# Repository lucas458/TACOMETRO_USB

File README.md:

# TACOMETRO USB
## Tacômetro USB para jogos usando PIC12F1822.

#### Placa

### Os dados a serem enviados são compostos por 6 bytes e serão transmitidos pela porta serial.
| Buffer Index | Valor (decimal) | Descrição |
| ------------ | --------------- | --------- |
| 0 | 0 a 255 | Digito 0 |
| 1 | 0 a 255 | Digito 1 |
| 2 | 0 a 255 | Digito 2 |
| 3 | 0 a 20 | Quantidade de LEDS ligados |
| 4 | 0 a 15 | Brilho |
| 5 | '\r' ou '\n' | **Caractere obrigatório** |

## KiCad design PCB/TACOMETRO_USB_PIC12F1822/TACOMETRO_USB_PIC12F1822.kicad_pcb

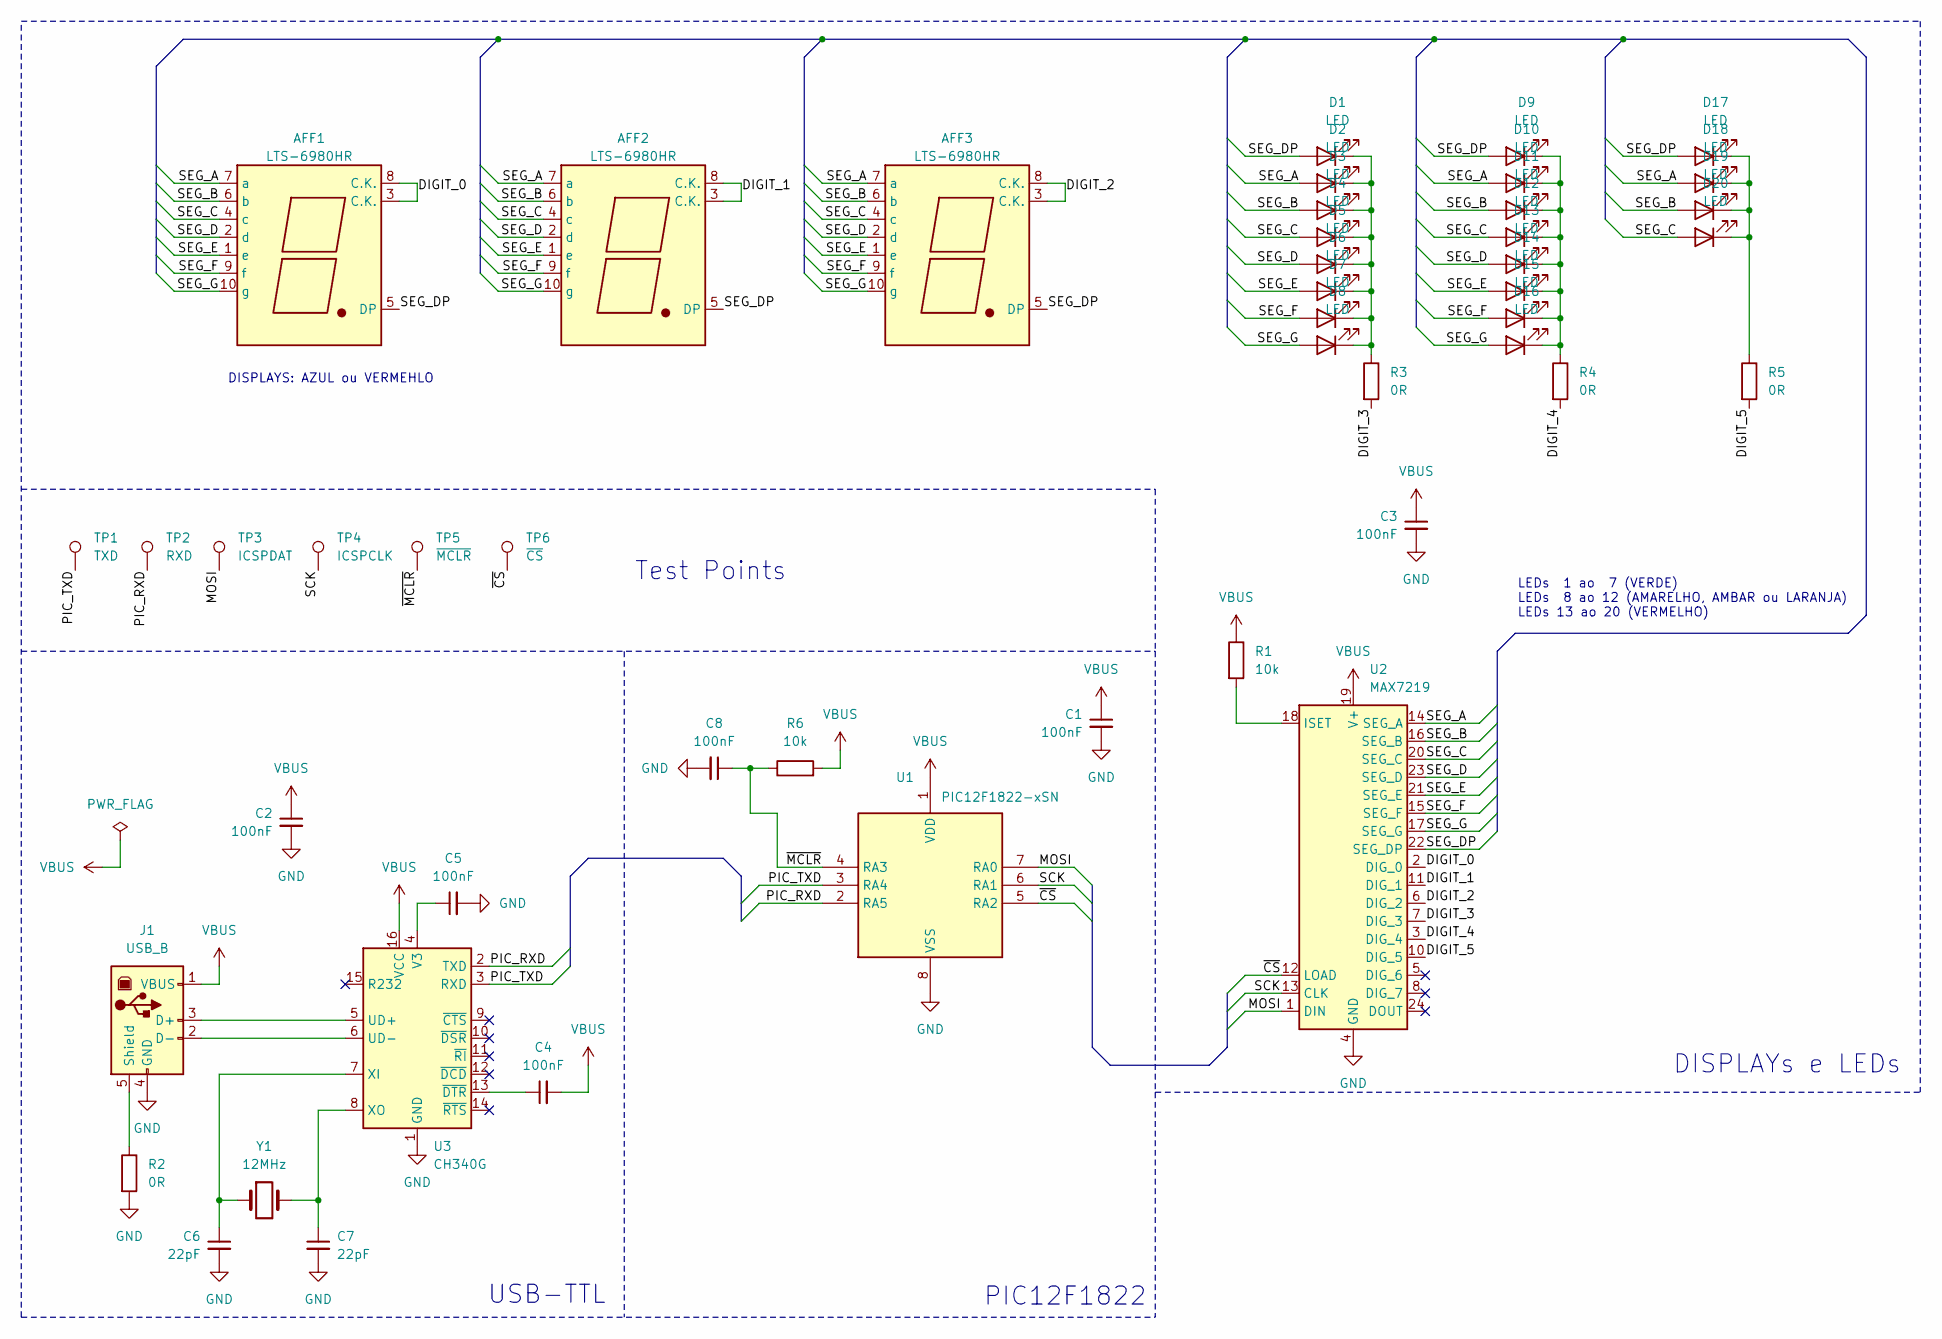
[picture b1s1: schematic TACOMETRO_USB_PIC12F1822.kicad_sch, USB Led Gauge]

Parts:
AFF1, AFF2, AFF3: LTS-6980HR; 7SegmentLED_LTS6760_LTS6780
C1, C2, C3, C4, C5, C8: 100nF; C_0603_1608Metric
C6, C7: 22pF; C_0603_1608Metric
D1, D2, D3, D4, D5, D6, D7, D8, D9, D10, D11, D12, D13, D14, D15, D16, D17, D18, D19, D20: LED; LED_D5.0mm_Clear
J1: USB_B; 5787834-1
R1, R6: 10k; R_0603_1608Metric
R2, R3, R4, R5: 0R; R_0603_1608Metric
TP1: TXD; TestPoint_Pad_D1.0mm
TP2: RXD; TestPoint_Pad_D1.0mm
TP3: ICSPDAT; TestPoint_Pad_D1.0mm
TP4: ICSPCLK; TestPoint_Pad_D1.0mm
TP5: ~{MCLR}; TestPoint_Pad_D1.0mm
TP6: ~{CS}; TestPoint_Pad_D1.0mm
U1: PIC12F1822-xSN; SOIC-8_3.9x4.9mm_P1.27mm
U2: MAX7219; SOIC-24W_7.5x15.4mm_P1.27mm
U3: CH340G; SOIC-16_3.9x9.9mm_P1.27mm
Y1: 12MHz; Crystal_HC49-U_Vertical

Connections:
/DIGIT_0: AFF1.3 (C.K.), AFF1.8 (C.K.), U2.2 (DIG_0)
/DIGIT_1: AFF2.3 (C.K.), AFF2.8 (C.K.), U2.11 (DIG_1)
/DIGIT_2: AFF3.3 (C.K.), AFF3.8 (C.K.), U2.6 (DIG_2)
/DIGIT_3: R3.2, U2.7 (DIG_3)
/DIGIT_4: R4.2, U2.3 (DIG_4)
/DIGIT_5: R5.2, U2.10 (DIG_5)
/MOSI: TP3.1, U1.7 (RA0), U2.1 (DIN)
/PIC_RXD: TP2.1, U1.2 (RA5), U3.2 (TXD)
/PIC_TXD: TP1.1, U1.3 (RA4), U3.3 (RXD)
/SCK: TP4.1, U1.6 (RA1), U2.13 (CLK)
/SEG_A: AFF1.7 (a), AFF2.7 (a), AFF3.7 (a), D2.2 (A), D10.2 (A), D18.2 (A), U2.14 (SEG_A)
/SEG_B: AFF1.6 (b), AFF2.6 (b), AFF3.6 (b), D3.2 (A), D11.2 (A), D19.2 (A), U2.16 (SEG_B)
/SEG_C: AFF1.4 (c), AFF2.4 (c), AFF3.4 (c), D4.2 (A), D12.2 (A), D20.2 (A), U2.20 (SEG_C)
/SEG_D: AFF1.2 (d), AFF2.2 (d), AFF3.2 (d), D5.2 (A), D13.2 (A), U2.23 (SEG_D)
/SEG_DP: AFF1.5 (DP), AFF2.5 (DP), AFF3.5 (DP), D1.2 (A), D9.2 (A), D17.2 (A), U2.22 (SEG_DP)
/SEG_E: AFF1.1 (e), AFF2.1 (e), AFF3.1 (e), D6.2 (A), D14.2 (A), U2.21 (SEG_E)
/SEG_F: AFF1.9 (f), AFF2.9 (f), AFF3.9 (f), D7.2 (A), D15.2 (A), U2.15 (SEG_F)
/SEG_G: AFF1.10 (g), AFF2.10 (g), AFF3.10 (g), D8.2 (A), D16.2 (A), U2.17 (SEG_G)
/~CS: TP6.1, U1.5 (RA2), U2.12 (LOAD)
/~MCLR: C8.1, R6.1, TP5.1, U1.4 (RA3)
GND: C1.2, C2.2, C3.2, C5.2, C6.2, C7.2, C8.2, J1.4 (GND), R2.2, U1.8 (VSS), U2.4 (GND), U2.9 (GND), U3.1 (GND)
unnamed: D1.1 (K), D2.1 (K), D3.1 (K), D4.1 (K), D5.1 (K), D6.1 (K), D7.1 (K), D8.1 (K), R3.1
unnamed: D9.1 (K), D10.1 (K), D11.1 (K), D12.1 (K), D13.1 (K), D14.1 (K), D15.1 (K), D16.1 (K), R4.1
unnamed: D17.1 (K), D18.1 (K), D19.1 (K), D20.1 (K), R5.1
unnamed: J1.3 (D+), U3.5 (UD+)
unnamed: J1.2 (D-), U3.6 (UD-)
unnamed: J1.5 (Shield), R2.1
unnamed: R1.2, U2.18 (ISET)
unnamed: C5.1, U3.4 (V3)
unnamed: C6.1, U3.7 (XI), Y1.1
unnamed: C7.1, U3.8 (XO), Y1.2
unnamed: C4.1, U3.13 (~DTR)
VBUS: C1.1, C2.1, C3.1, C4.2, J1.1 (VBUS), R1.1, R6.2, U1.1 (VDD), U2.19 (V+), U3.16 (VCC)

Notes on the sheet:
Test Points
USB-TTL
LEDs 1 ao 7 (VERDE) LEDs 8 ao 12 (AMARELHO, AMBAR ou LARANJA) LEDs 13 ao 20 (VERMELHO)
DISPLAYS: AZUL ou VERMEHLO
PIC12F1822
DISPLAYs e LEDs

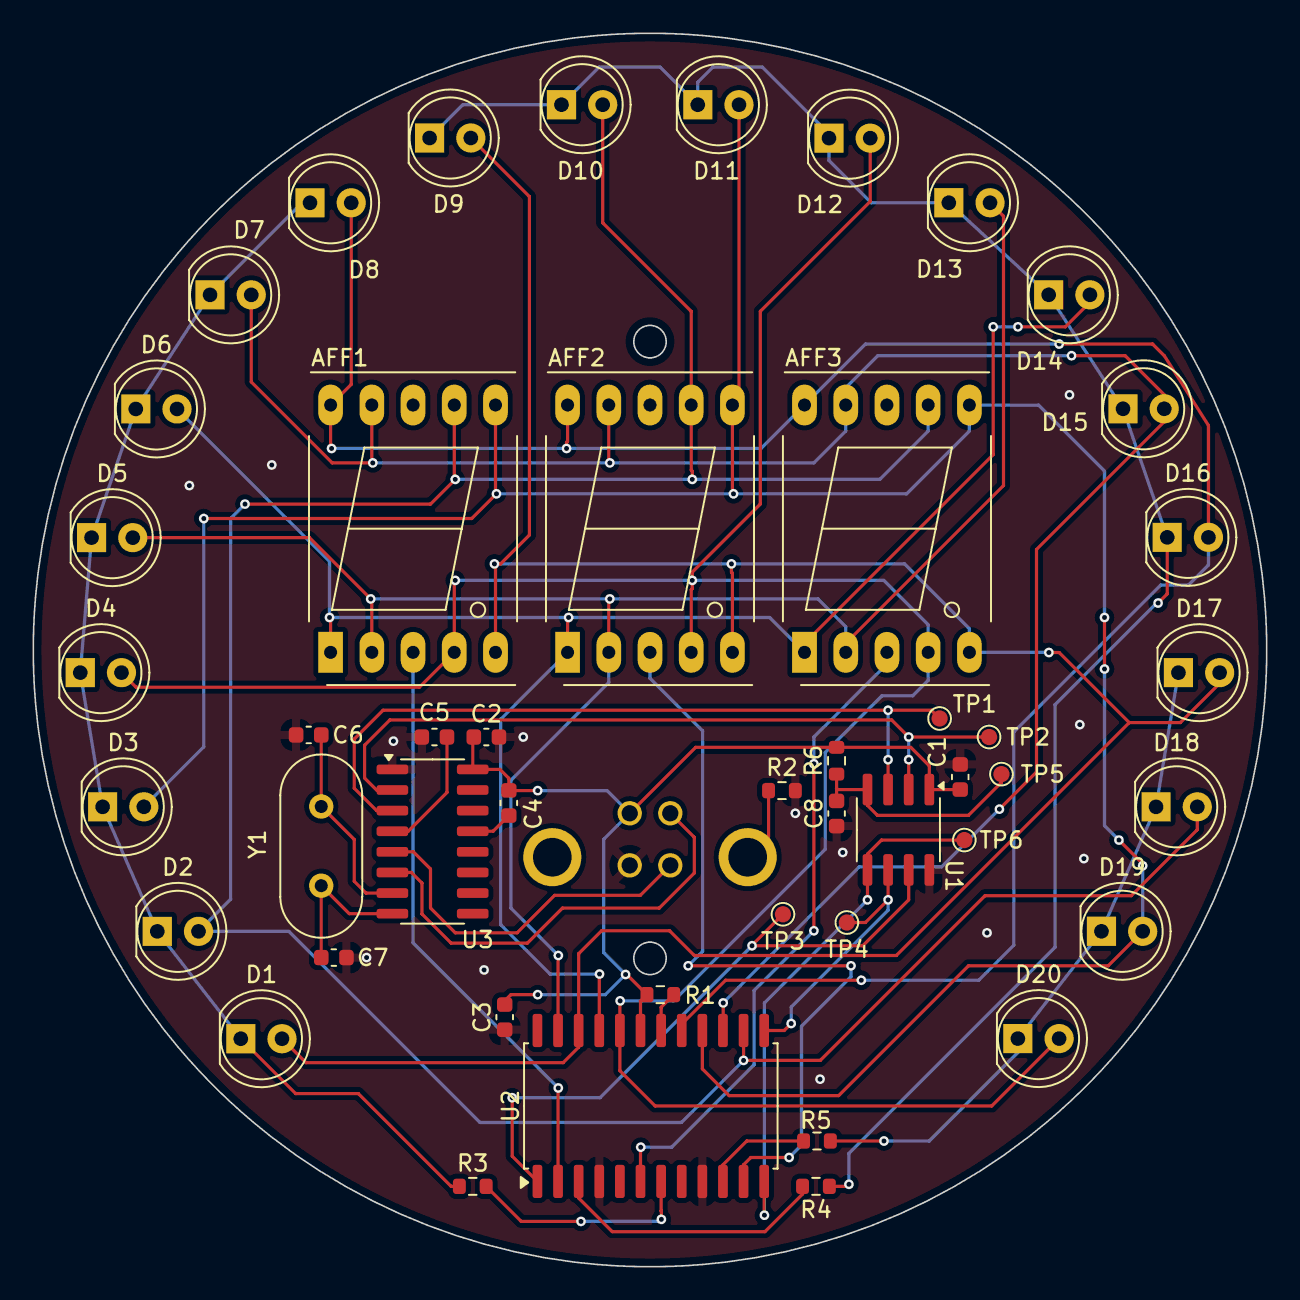
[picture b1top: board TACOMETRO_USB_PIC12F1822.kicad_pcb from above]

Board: 2 copper layers, 76.0 x 76.0 mm, 48 parts (1 on the bottom side), 33 nets.
